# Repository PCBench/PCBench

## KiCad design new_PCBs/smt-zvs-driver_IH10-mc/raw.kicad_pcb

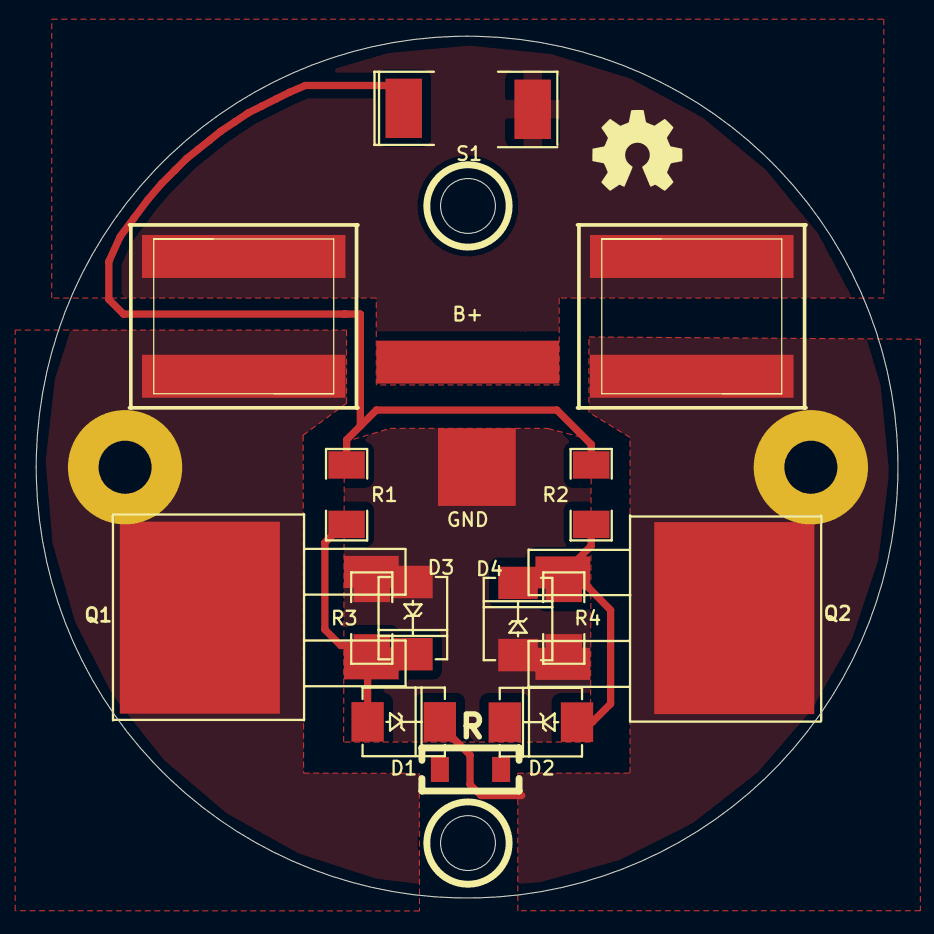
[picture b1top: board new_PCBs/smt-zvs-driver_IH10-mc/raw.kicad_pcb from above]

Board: 2 copper layers, 47.9 x 47.9 mm, 19 parts (0 on the bottom side), 7 nets.

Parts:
B+: Pad-B+
D1, D2: DIODE; DO214
D3, D4: ZENER; DO214
GND: Pad-Gnd
L1, L2: INDUCTOR; inductor-coilcraft-xal1010-102
Q1: MOSFET_N; DPAKGDS-Q1
Q2: MOSFET_N; DPAKGDS-Q2
R: Resistor_SMD1206_ReflowWave_RevA_Date21Jun2010; Resistor_SMD1206_ReflowWave
R1, R2: 270; SM1206
R3, R4: 10K; SM1206
S1: Val**; SM2112L
endcap: VAL**; endcap-ss
mount: P***; 1pin
mount#2: P***; 1pin

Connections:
+BATT: L1.1, L2.1, S1.2
GND: D3.1, D4.1, GND.1, Q1.S, Q2.S, R3.2, R4.2
unnamed: D2.1, D4.2, Q2.G, R2.2, R4.1
unnamed: D1.1, D3.2, Q1.G, R1.2, R3.1
unnamed: R1.1, R2.1, S1.1
unnamed: D2.2, L1.2, Q1.D
unnamed: D1.2, L2.2, Q2.D

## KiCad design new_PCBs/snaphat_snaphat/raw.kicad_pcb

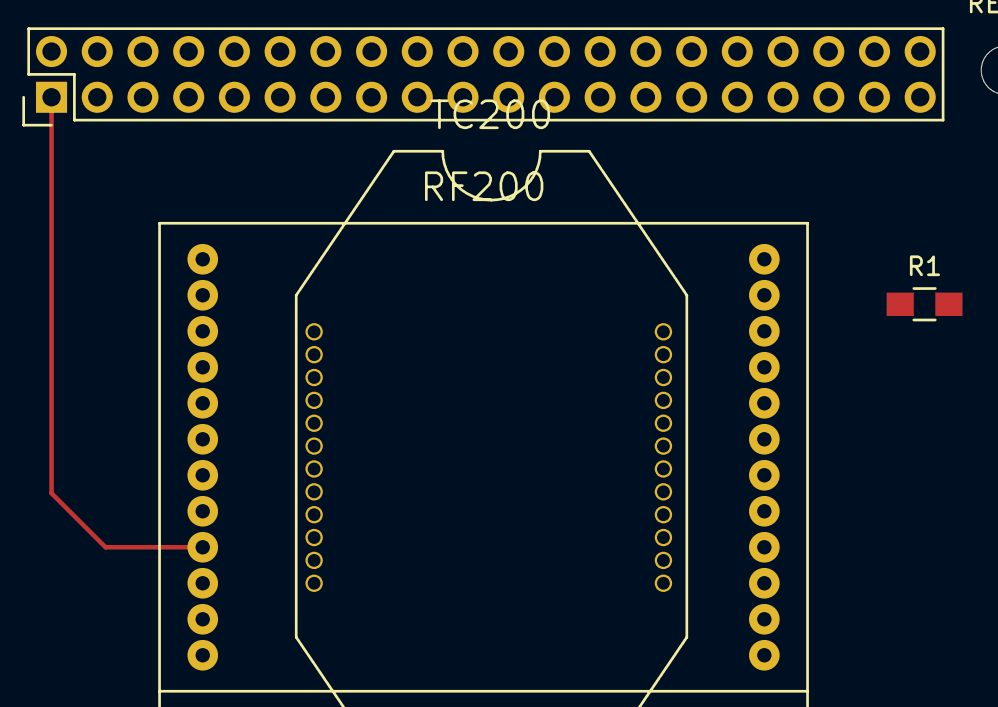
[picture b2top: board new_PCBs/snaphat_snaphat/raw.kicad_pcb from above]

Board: 2 copper layers, 4 parts (0 on the bottom side), 5 nets.

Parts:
J1: RPi_GPIO; Pin_Header_Straight_2x20
R1: R; R_0805_HandSoldering
U1: TC200
U2: RF200

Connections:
3v3: J1.1, R1.2, U1.17, U2.21
GND: J1.9, U1.19, U2.1
RST: J1.18, R1.1, U1.18, U2.23
RX_PI: J1.10, U1.21, U2.10
TX_PI: J1.8, U1.20, U2.9

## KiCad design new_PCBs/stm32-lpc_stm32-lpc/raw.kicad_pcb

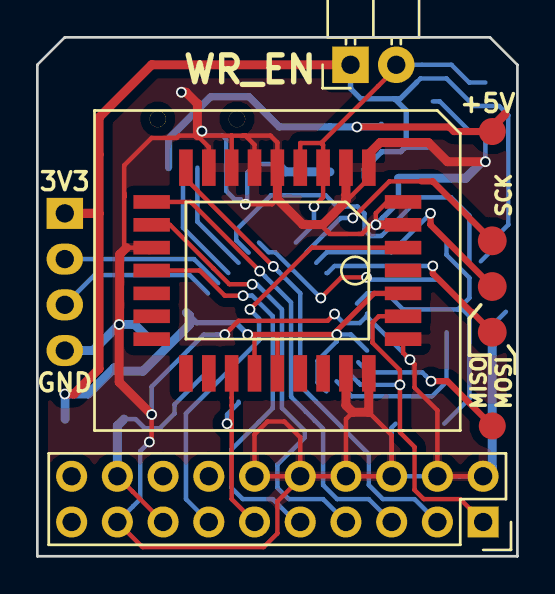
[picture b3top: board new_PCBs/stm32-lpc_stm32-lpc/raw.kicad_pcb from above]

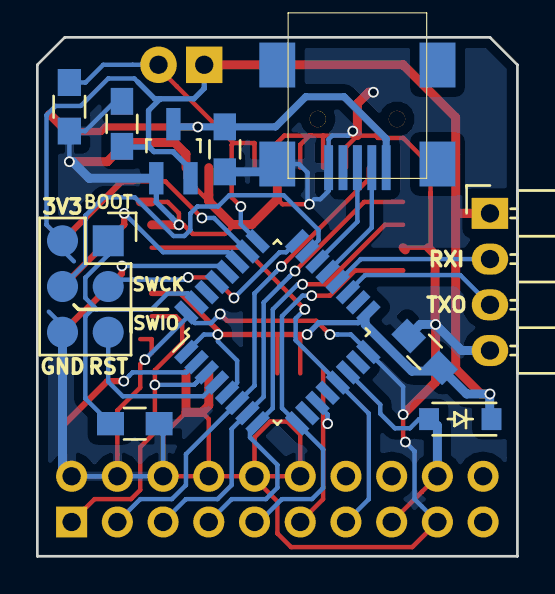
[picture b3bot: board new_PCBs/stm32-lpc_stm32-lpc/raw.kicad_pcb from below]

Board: 2 copper layers, 26.7 x 28.8 mm, 19 parts (11 on the bottom side), 24 nets.

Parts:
C1, C2, C3: 1u; C_0805_HandSoldering
CON1: SWD_BOOT_CS-6; Socket_Strip_Straight_2x03
D1: D_Schottky_Small; SOD-123
JP1: JUMPER; Pin_Header_Angled_1x02
P1: CONN_02X10; Socket_Strip_Straight_2x10
P2: CONN_01X04; Pin_Header_Angled_1x04
P3: USB_OTG; USB-MINI-B-SMD
P4, P5, P6, P7, P8: CONN_01X01; TSTPT
R1, R2: 4k7; R_0805_HandSoldering
U1: Pm49FL004; PLCC-32
U2: STM32F042Kx; LQFP-32_7x7mm_Pitch0.8mm
U3: MCP1700; SOT-23_Handsoldering

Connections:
/3V3IN: D1.2, P1.15, P1.18, U2.14
/BOOT0: CON1.1, R2.1, U2.31
/CLK: P1.1, U1.31, U2.3
/D0: P1.3, U1.13, U2.6
/D1: P1.5, U1.14, U2.7
/D2: P1.7, U1.15, U2.8
/D3: P1.9, U1.17, U2.9
/D+: P3.3, U2.22
/D-: P3.2, U2.21
/MISO: P5.1, U2.27
/MOSI: P4.1, U2.28
/RXD: P2.2, U2.20
/SCK: P6.1, U2.26
/SPIOE: P7.1, U2.2
/SWCLK: CON1.3, U2.24
/SWDIO: CON1.4, U2.23
/TXD: P2.3, U2.19
/VBUS: C2.1, P3.1, P8.1, U3.3
/~LFRAME: P1.11, U1.23, U2.11
/~RST: P1.13, U1.2, U2.13
/~SRST: CON1.5, U2.4
/~WP: JP1.2, R1.1, U1.7, U1.8, U2.25
GND: C1.2, C2.2, C3.2, CON1.6, P1.2, P1.4, P1.6, P1.8, P1.10, P1.12, P1.17, P2.4, P3.5, P3.6, R1.2, R2.2, U1.3, U1.4, U1.5, U1.6, U1.9, U1.10, U1.11, U1.12, U1.16, U1.28, U1.29, U1.30, U2.16, U2.32, U3.1
VCC: C1.1, C3.1, CON1.2, D1.1, JP1.1, P2.1, U1.24, U1.25, U1.32, U2.1, U2.5, U2.17, U3.2

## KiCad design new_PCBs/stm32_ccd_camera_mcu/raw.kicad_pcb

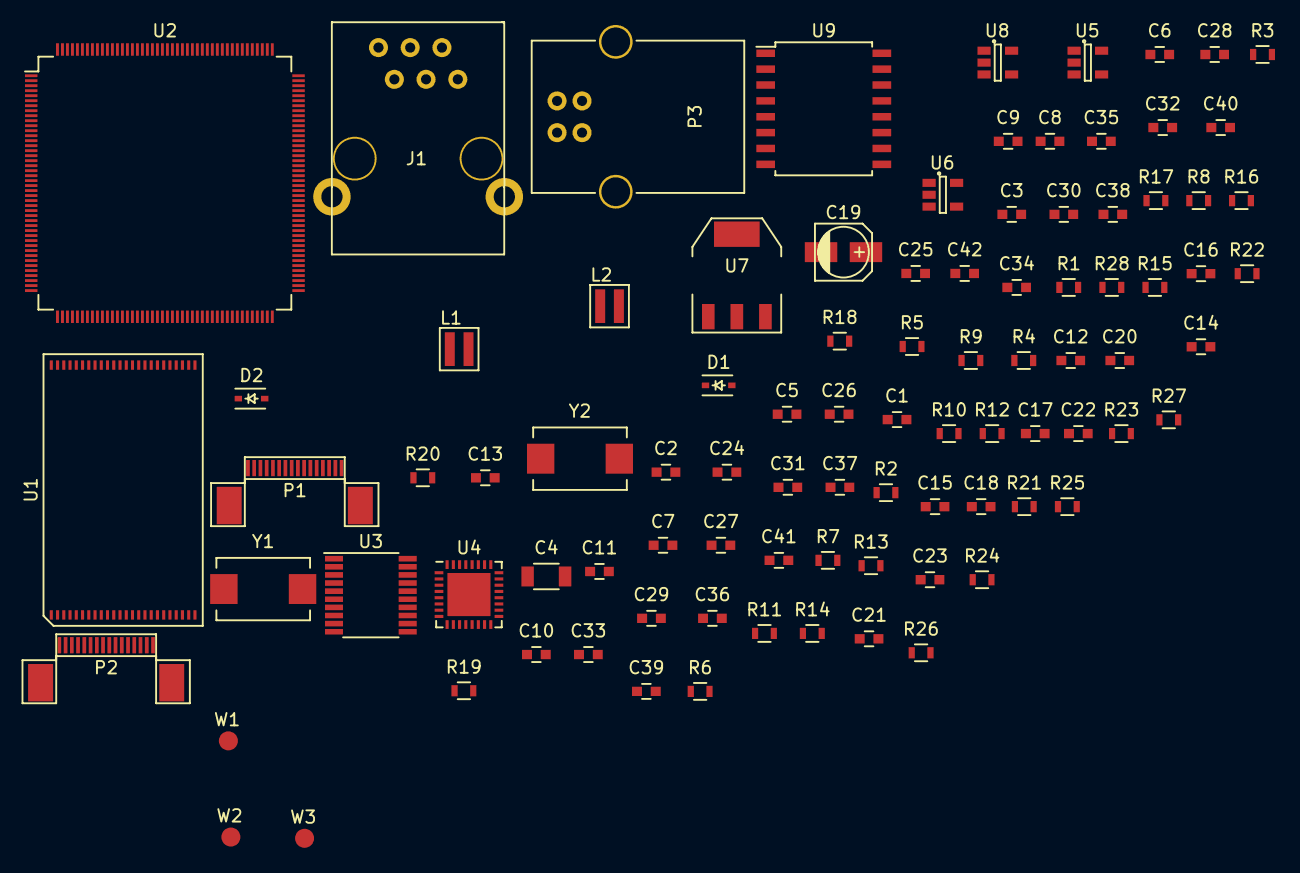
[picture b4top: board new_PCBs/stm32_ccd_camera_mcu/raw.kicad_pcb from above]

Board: 2 copper layers, 92 parts (0 on the bottom side), 130 nets, no tracks yet.

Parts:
C1, C2, C21, C23, C24, C27, C29, C31, C32, C33, C34, C35, C36: 100nf; C_0603
C3, C5, C16: 47nf; C_0603
C4: 10uf; C_1206
C6, C7: 4.7uf; C_0603
C8, C9, C10, C11, C17, C18, C22: 1uf; C_0603
C12, C13, C37, C38: 22p; C_0603
C14, C15: 10uf; C_0603
C19: 47uf; c_elec_4x5.3
C20, C28: 4.7nf; C_0603
C25, C26, C30, C40, C41: 2.2uf; C_0603
C39: 0.1uf; C_0603
C42: 47n; C_0603
D1, D2: DFLS240/NSR0320MW2T1G; SOD-323
J1: RJ12; RJ12_EQMAX
L1: 6.8uH; Choke_SMD_3x3_H1.5
L2: 3.3uH; Choke_SMD_3x3_H1.5
P1, P2: CONN_01X16; FPC_16
P3: USB_B
R1, R22: 10K; R_0603
R2: 5.6K; R_0603
R3: 12k; R_0603
R4: 2.1M; R_0603
R5: 2.15M; R_0603
R6: 100k; R_0603
R7: 12K; R_0603
R8: 820; R_0603
R9: 113K; R_0603
R10, R11, R21, R28: 1M; R_0603
R12: 20k; R_0603
R13: 10k; R_0603
R14: 147k; R_0603
R15, R17: 13k; R_0603
R16, R24, R25, R26, R27: 1k; R_0603
R18, R19, R20: R_Small; R_0603
R23: 510; R_0603
U1: IS64WV102416; TSSOP_48_12X20mm_Pitch0.5mm
U2: stm32f429igt6; LQFP-176_20x20mm_Pitch0.4mm
U3: ADP5070; TSSOP-20_4.4x6.5mm_Pitch0.65mm
U4: USB3300; QFN-32-1EP_5x5mm_Pitch0.5mm
U5, U8: ADP7142; SOT-23-5
U6: ADP7182; SOT-23-5
U7: LM1117-3.3; SOT-223
U9: TLP291-4; SOIC-16_7.5x10.3mm_Pitch1.27mm
W1: BOOT; TP_SMD
W2: TXD; TP_SMD
W3: RXD; TP_SMD
Y1: 24M; Crystal_FOX-FE_SMD
Y2: 8M; Crystal_FOX-FE_SMD

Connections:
+3V3: C1.1, C2.1, C9.2, C24.1, C27.1, C29.1, C31.1, C32.1, C33.1, C34.1, C35.1, C36.1, R1.1, R22.2, U1.12, U1.36, U2.6, U2.15, U2.23, U2.36, U2.38, U2.39, U2.49, U2.62, U2.72, U2.82, U2.91, U2.103, U2.114, U2.127, U2.136, U2.149, U2.159, U2.171, U2.172, U4.6, U4.16, U4.25, U4.30, U4.31, U7.2, U7.4, U9.1, U9.3, U9.5, U9.7
+5V: C4.2, C10.1, C19.1, C20.2, C21.1, P3.1, R8.2, U3.9, U3.11, U3.17, U3.18, U3.19, U7.3, U8.1, U8.3
/15V: C22.1, C25.1, P2.4, R12.1, U5.5
/16V: C14.2, C17.2, D2.1, R5.1, U5.1, U5.3
/+4.85V: C28.1, C30.1, P2.5, R18.1, U8.5
/-9V: C23.1, C26.1, P2.3, R14.1, U6.5
/-10V: C15.1, C18.2, D1.2, R4.2, U6.2, U6.3
/ADCCLK: P1.3, U2.129
/ADC_D0: P1.16, U2.131
/ADC_D1: P1.15, U2.132
/ADC_D2: P1.14, U2.133
/ADC_D3: P1.13, U2.134
/ADC_D4: P1.12, U2.173
/ADC_D5: P1.11, U2.174
/ADC_D6: P1.10, U2.175
/ADC_D7: P1.9, U2.176
/BOOT0: R23.1, U2.166, W1.1
/CDSCLK1: P1.5, U2.89
/CDSCLK2: P1.4, U2.128
/DEC+: R26.1, U2.167
/DEC-: R25.1, U2.165
/MCU_H1: P2.9, U2.86
/MCU_H2: P2.8, U2.87
/MCU_RG: P2.7, U2.88
/MCU_XSG1: P2.13, U2.46
/MCU_XSG2: P2.11, U2.84
/MCU_XSHT: P2.16, U2.43
/MCU_XV1: P2.14, U2.45
/MCU_XV2: P2.15, U2.44
/MCU_XV3: P2.12, U2.83
/MCU_XV4: P2.10, U2.85
/NRST: C39.1, R22.1, U2.31
/OSC_IN: C37.2, R21.2, U2.29, Y2.1
/OSC_OUT: C38.2, R21.1, U2.30, Y2.2
/PD0: U1.10, U2.142
/PD1: U1.11, U2.143
/PD4: U1.44, U2.146
/PD5: U1.18, U2.147
/PD7: R1.2, U1.7, U2.151
/PD11: U1.23, U2.99
/PD12: U1.22, U2.100
/PD13: U1.21, U2.101
/PD14: U1.8, U2.104
/PD15: U1.9, U2.105
/PE0: U1.42, U2.169
/PE1: U1.43, U2.170
/PE3: U1.20, U2.2
/PE7: U1.14, U2.68
/PE8: U1.15, U2.69
/PE9: U1.16, U2.70
/PE10: U1.17, U2.73
/PE11: U1.32, U2.74
/PE12: U1.33, U2.75
/PE13: U1.34, U2.76
/PE14: U1.35, U2.77
/PE15: U1.38, U2.78
/PF0: U1.5, U2.16
/PF1: U1.4, U2.17
/PF2: U1.3, U2.18
/PF3: U1.2, U2.19
/PF4: U1.1, U2.20
/PF5: U1.48, U2.21
/PF12: U1.47, U2.60
/PF13: U1.46, U2.63
/PF14: U1.45, U2.64
/PF15: U1.30, U2.65
/PG0: U1.29, U2.66
/PG1: U1.28, U2.67
/PG2: U1.27, U2.106
/PG3: U1.26, U2.107
/PG4: U1.25, U2.108
/PG5: U1.24, U2.109
/RA+: R27.1, U2.168
/RA-: R24.1, U2.164
/SCLK: P1.8, U2.7
/SDATA: P1.7, U2.11
/SLOAD: P1.6, U2.12
/ULPI_CLK: U2.51, U4.14
/ULPI_D0: U2.47, U4.24
/ULPI_D1: U2.56, U4.23
/ULPI_D2: U2.57, U4.22
/ULPI_D3: U2.79, U4.21
/ULPI_D4: U2.80, U4.20
/ULPI_D5: U2.92, U4.19
/ULPI_D6: U2.93, U4.18
/ULPI_D7: U2.163, U4.17
/ULPI_DIR: U2.34, U4.12
/ULPI_NXT: U2.35, U4.11
/ULPI_STP: U2.32, U4.13
/VCAP_1: C40.2, U2.81
/VCAP_2: C41.2, U2.125
GND: C1.2, C2.2, C3.2, C4.1, C5.2, C6.2, C7.2, C8.1, C9.1, C10.2, C11.2, C12.1, C13.1, C14.1, C15.2, C16.1, C17.1, C18.1, C19.2, C20.1, C21.2, C24.2, C25.2, C26.2, C27.2, C29.2, C30.2, C31.2, C32.2, C33.2, C34.2, C35.2, C36.2, C37.1, C38.1, C39.2, C40.1, C41.1, C42.1, L1.2, P1.1, P1.2, P2.1, P2.2, P2.6, P3.4, R7.1, R9.1, R11.1, R13.2, R15.2, R19.2, R23.2, R28.2, U1.13, U1.37, U2.14, U2.22, U2.37, U2.48, U2.61, U2.71, U2.90, U2.102, U2.113, U2.126, U2.135, U2.148, U2.158, U3.1, U3.4, U3.15, U4.1, U4.2, U4.33, U5.2, U6.1, U7.1, U8.2
unnamed: C3.1, R2.1
unnamed: C5.1, R3.1
unnamed: C6.1, U4.15, U4.26
unnamed: C7.1, U4.29
unnamed: C8.2, U3.16
unnamed: C11.1, R6.1, U3.14
unnamed: C12.2, R10.2, U4.27, Y1.1
unnamed: C13.2, R10.1, U4.28, Y1.2
unnamed: C16.2, P3.5, R11.2
unnamed: C22.2, R16.1
unnamed: C23.2, R17.1
unnamed: C28.2, R20.1
unnamed: C42.2, J1.7, J1.8, R28.1
unnamed: D1.1, L1.1, U3.20
unnamed: D2.2, L2.2, U3.2
unnamed: J1.2, U9.9, U9.11, U9.13, U9.15
unnamed: J1.3, U9.10
unnamed: J1.4, U9.12
unnamed: J1.5, U9.14
unnamed: J1.6, U9.16
unnamed: L2.1, U3.3
unnamed: P3.2, U4.8
unnamed: P3.3, U4.7
unnamed: R2.2, U3.8
unnamed: R3.2, U3.12
unnamed: R4.1, R6.2, U3.13
unnamed: R5.2, R9.2, U3.7
unnamed: R7.2, U4.32
unnamed: R8.1, U4.4
unnamed: R12.2, R13.1, R16.2, U5.4
unnamed: R14.2, R15.1, R17.2, U6.4
unnamed: R18.2, R19.1, R20.2, U8.4
unnamed: R24.2, U9.2
unnamed: R25.2, U9.4
unnamed: R26.2, U9.6
unnamed: R27.2, U9.8
unnamed: U2.120, W2.1
unnamed: U2.121, W3.1
